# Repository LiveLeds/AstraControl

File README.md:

# AstraControl

[GitHub IO Page](https://liveleds.github.io/AstraControl)

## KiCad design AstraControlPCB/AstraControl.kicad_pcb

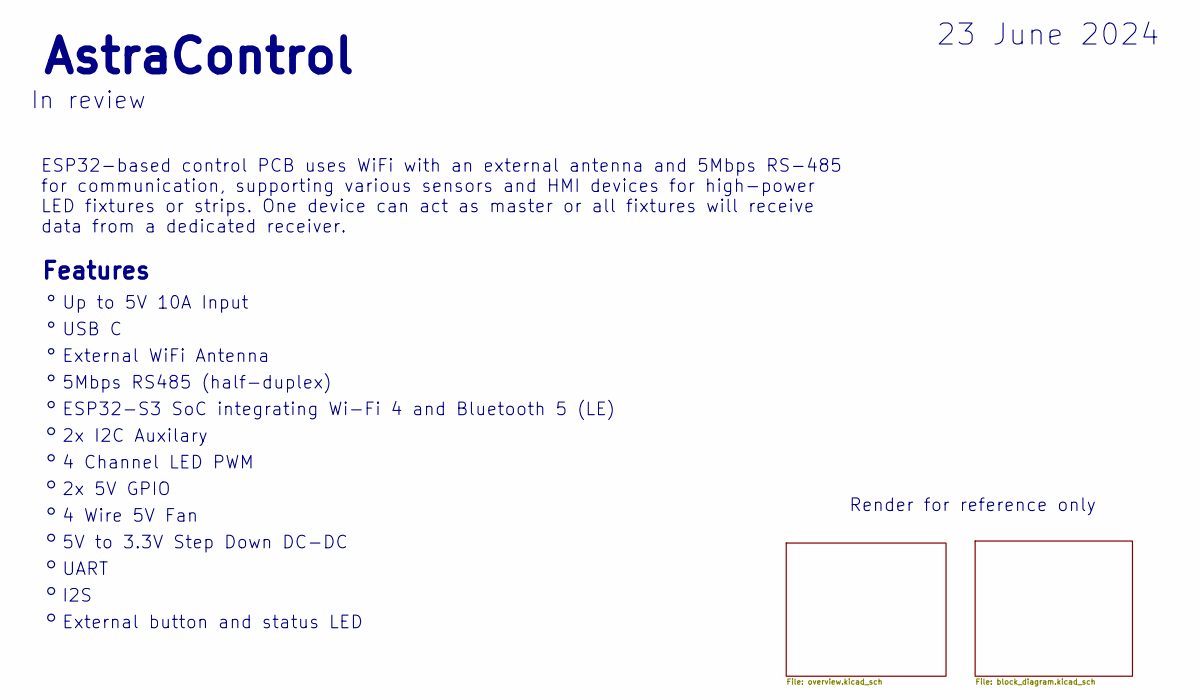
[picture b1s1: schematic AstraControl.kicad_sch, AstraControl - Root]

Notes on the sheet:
2x 5V GPIO
I2S
USB C
2x I2C Auxilary
Render for reference only
23 June 2024
ESP32-based control PCB uses WiFi with an external antenna and 5Mbps RS-485 for communication, supporting various sensors and HMI devices for high-power LED fixtures or strips. One device can act as master or all fixtures will receive data from a dedicated receiver.
AstraControl
5V to 3.3V Step Down DC-DC
External WiFi Antenna
ESP32-S3 SoC integrating Wi-Fi 4 and Bluetooth 5 (LE)
In review
Up to 5V 10A Input
4 Channel LED PWM
UART
External button and status LED
Features
5Mbps RS485 (half-duplex)
4 Wire 5V Fan

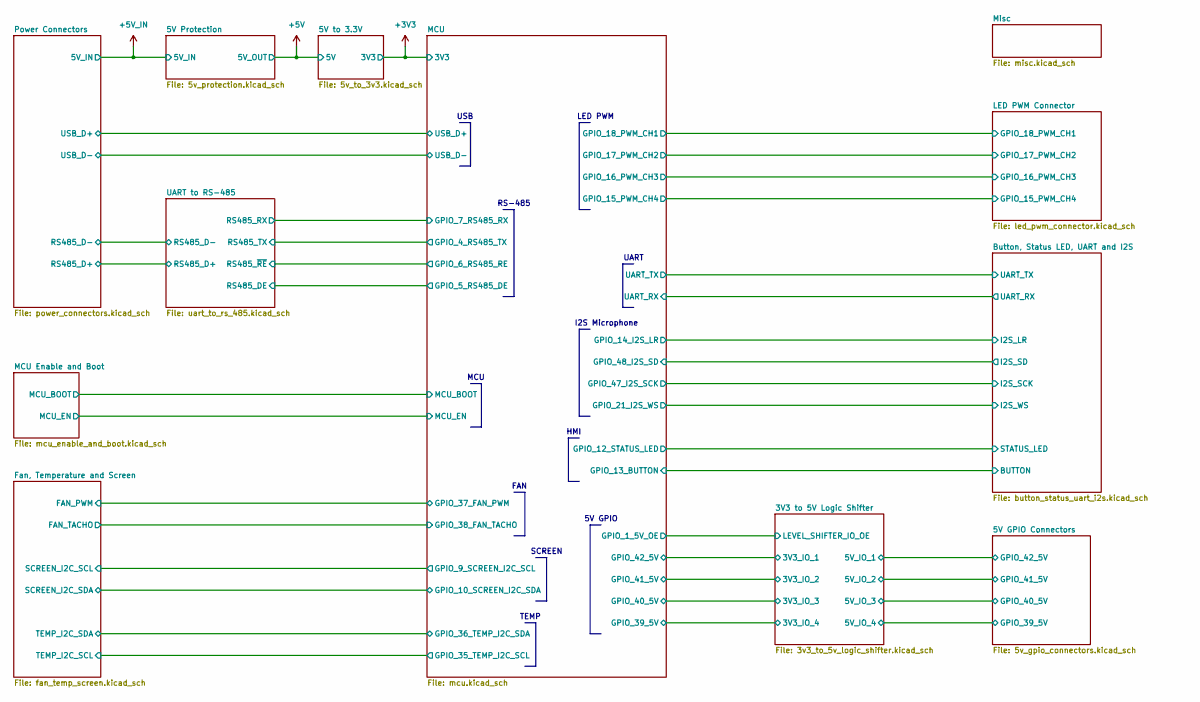
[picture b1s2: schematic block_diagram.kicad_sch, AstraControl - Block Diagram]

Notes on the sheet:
USB
FAN
LED PWM
MCU
I2S Microphone
5V GPIO
RS-485
UART
SCREEN
HMI
TEMP

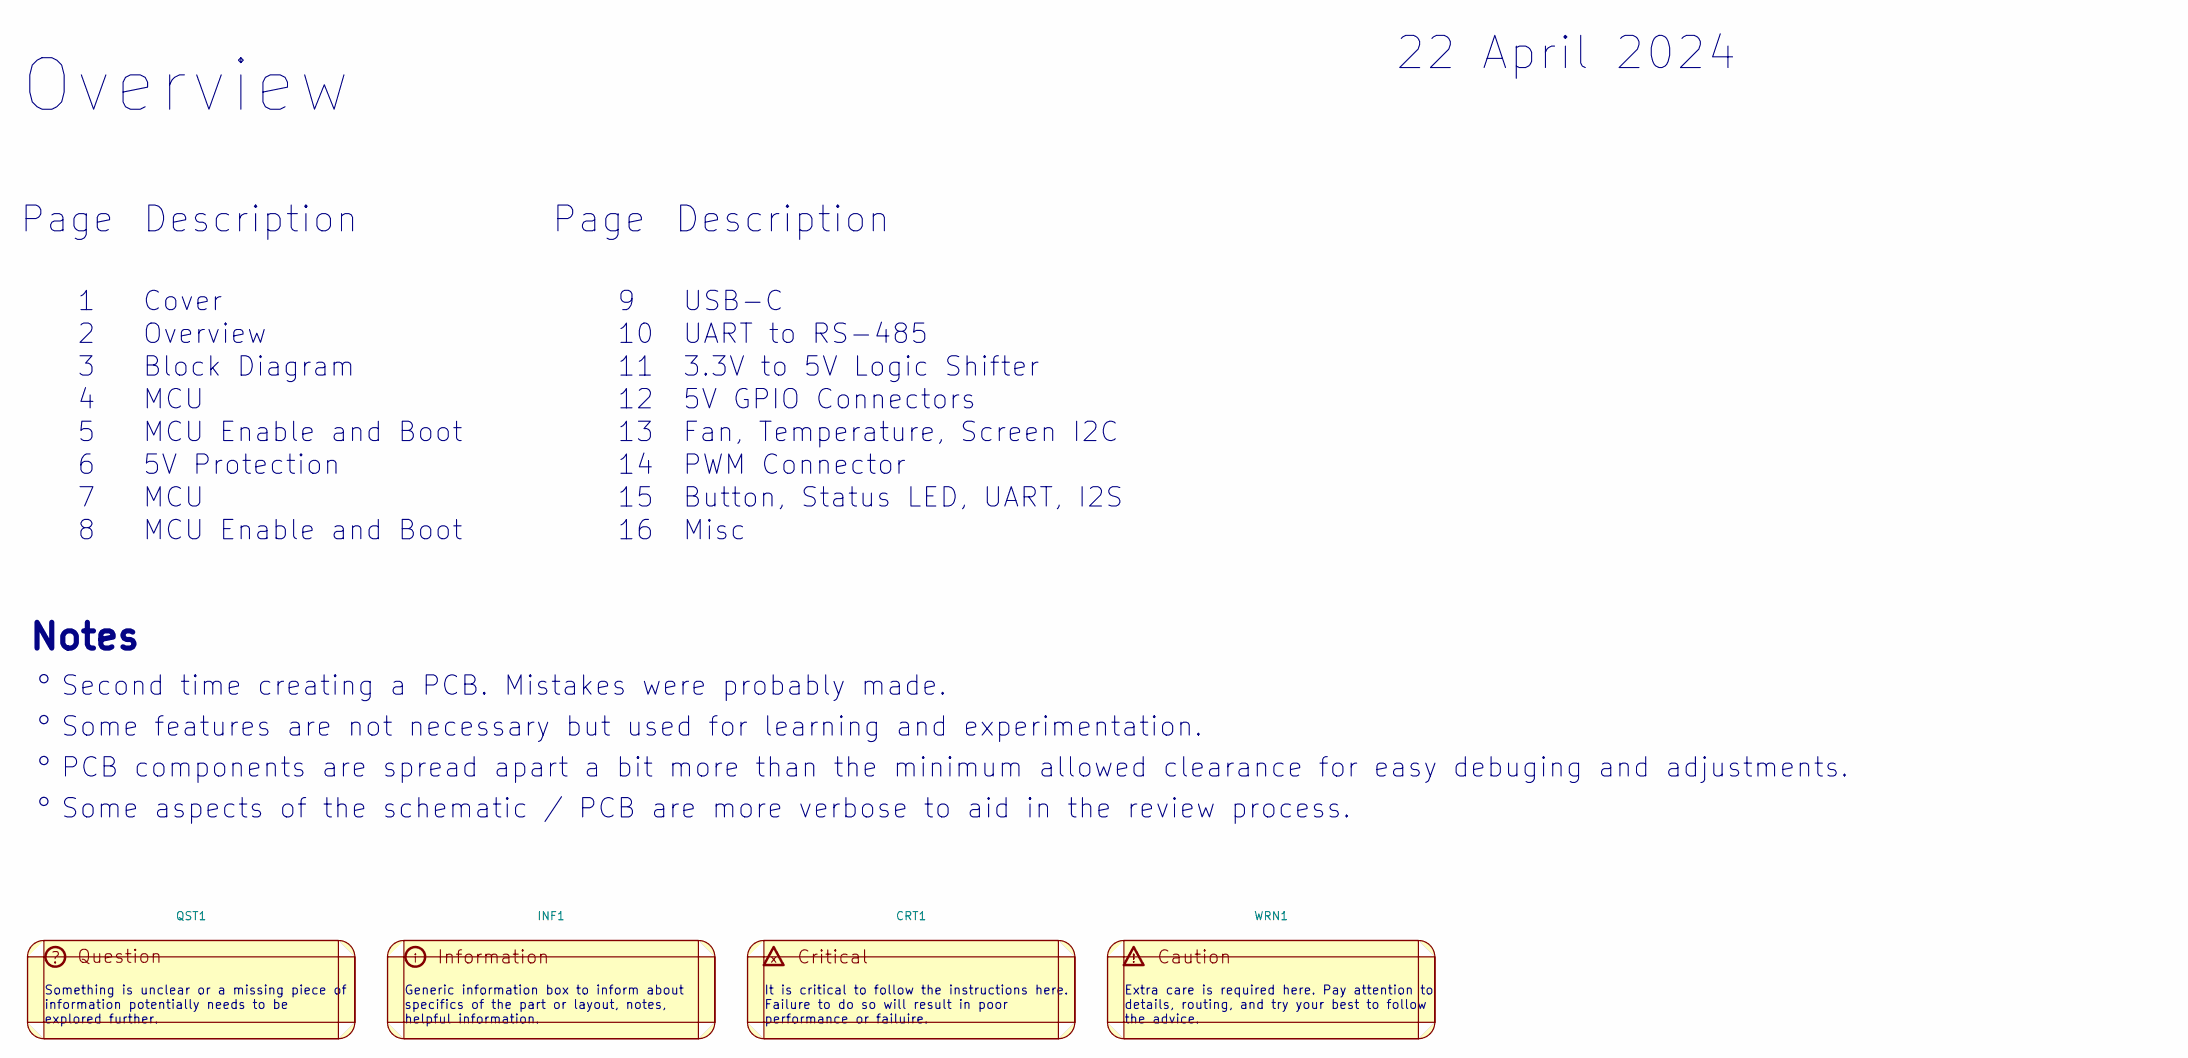
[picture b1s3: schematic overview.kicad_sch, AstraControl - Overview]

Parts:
CRT1: (no value)
INF1: (no value)
QST1: (no value)
WRN1: (no value)

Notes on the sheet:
Some features are not necessary but used for learning and experimentation.
PWM Connector
Misc
3.3V to 5V Logic Shifter
UART to RS-485
Fan, Temperature, Screen I2C
5V Protection
PCB components are spread apart a bit more than the minimum allowed clearance for easy debuging and adjustments.
Something is unclear or a missing piece of information potentially needs to be explored further.
Page
22 April 2024
MCU Enable and Boot
Notes
5V GPIO Connectors
It is critical to follow the instructions here. Failure to do so will result in poor performance or failuire.
Overview
Cover
MCU
Second time creating a PCB. Mistakes were probably made.
Description
Some aspects of the schematic / PCB are more verbose to aid in the review process.
Button, Status LED, UART, I2S
USB-C
Generic information box to inform about specifics of the part or layout, notes, helpful information.
Extra care is required here. Pay attention to details, routing, and try your best to follow the advice.
Block Diagram

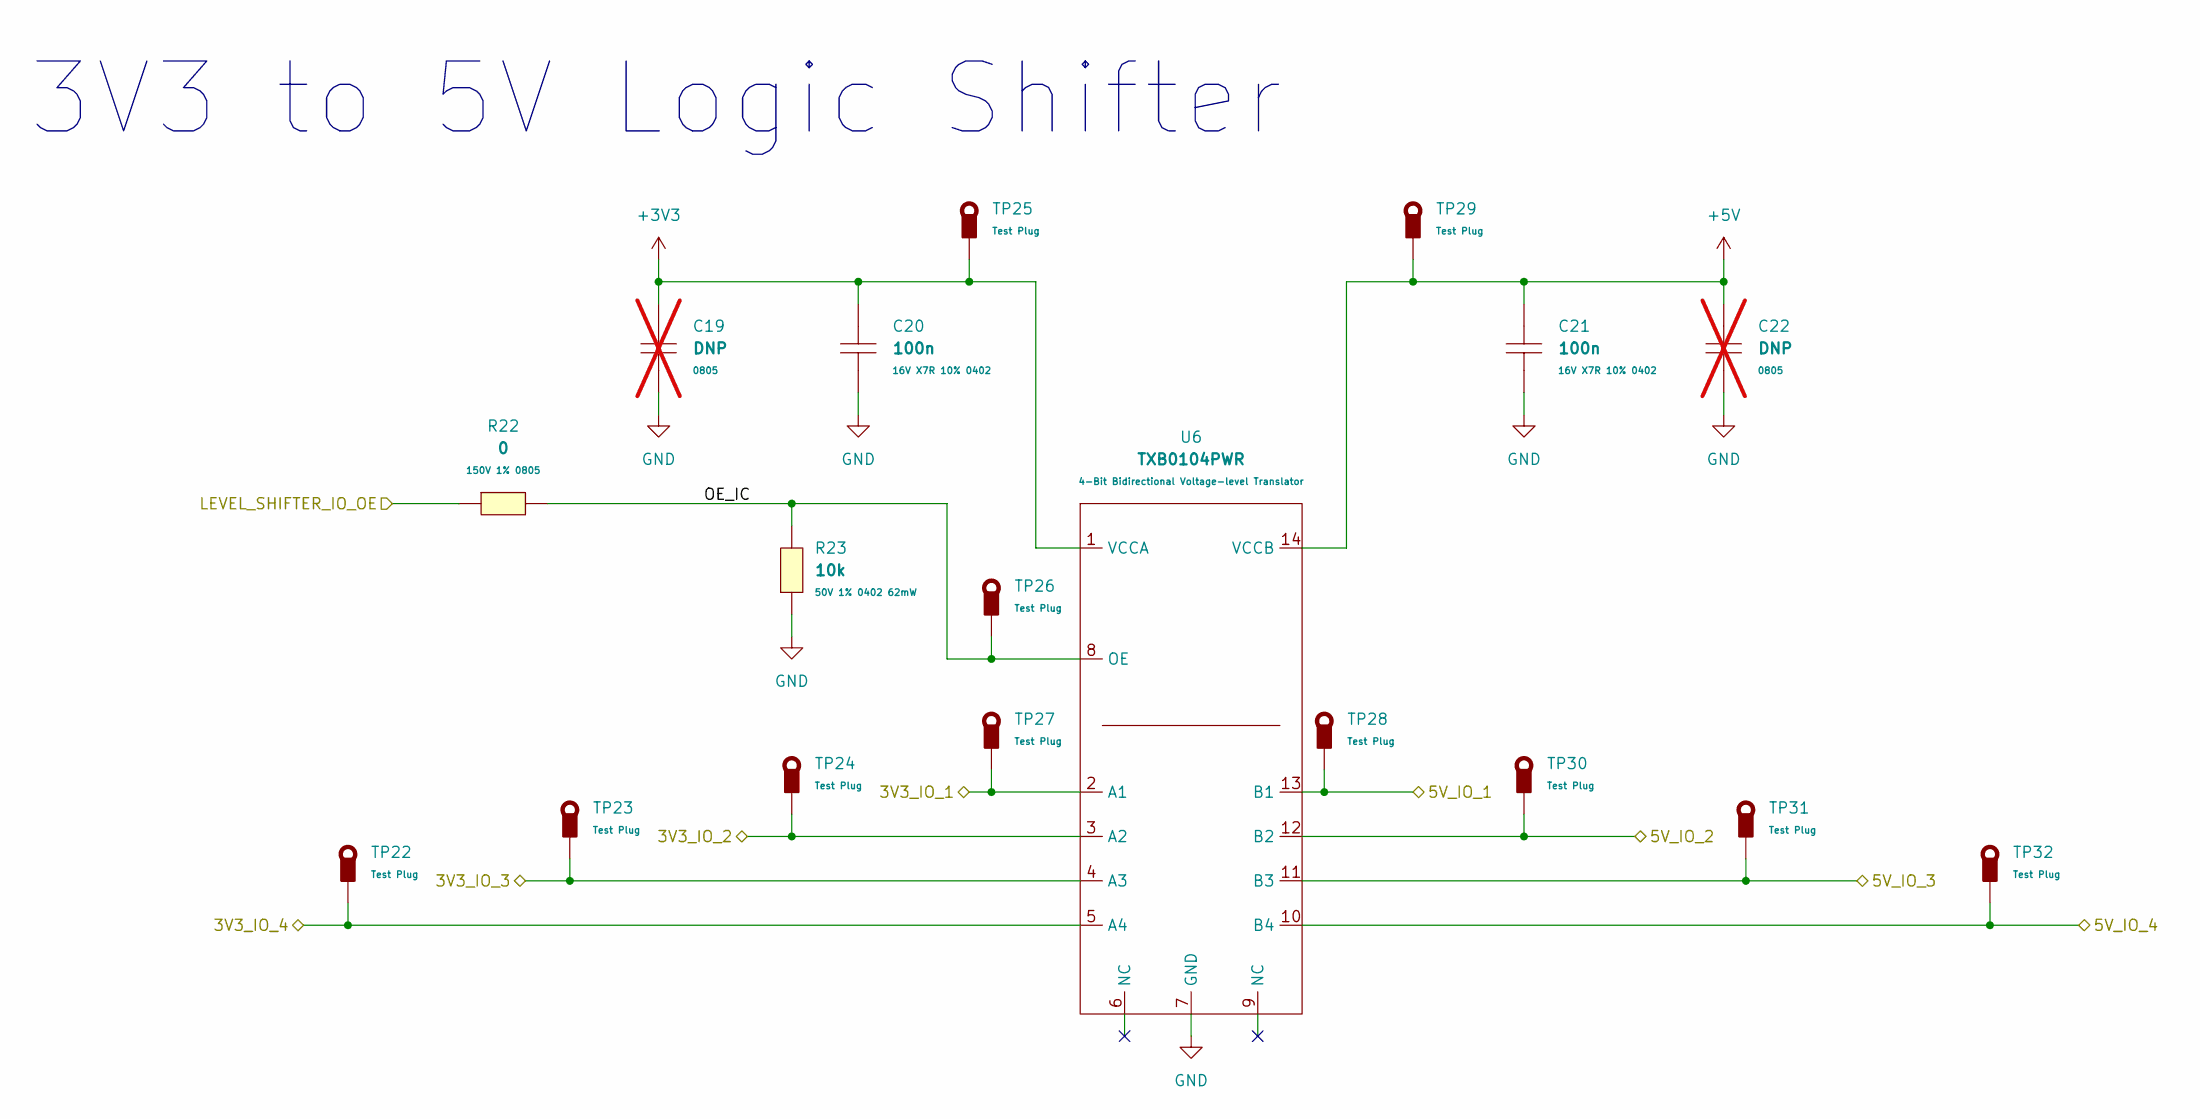
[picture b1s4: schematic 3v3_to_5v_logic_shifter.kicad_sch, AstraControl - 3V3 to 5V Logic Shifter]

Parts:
C19, C22: DNP; C_DNP_0805_2012Metric_Pad1.18x1.45mm_HandSolder; not fitted
C20, C21: 100n; C_0402_1005Metric; MPN CL05B104KO5NNNC; LCSC Part C1525
R22: 0; R_0805_2012Metric_Pad1.20x1.40mm_HandSolder; MPN 0805W8F0000T5E; LCSC Part C17477
R23: 10k; R_0402_1005Metric; MPN 0402WGF1002TCE; LCSC Part C25744
TP22, TP23, TP24, TP25, TP26, TP27, TP28, TP29, TP30, TP31, TP32: TestPoint_Thimble; TestPoint_Loop_D3.50mm_Drill0.9mm_Beaded; MPN RH-5000; LCSC Part C5277086
U6: TXB0104PWR; LOGIC_SHIFTER_TXB0104PWR_TSOP_14; MPN TXB0104PWR; LCSC Part C60708

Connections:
+3V3: C19.2, C20.2, TP25.1, U6.1 (VCCA); also elsewhere on the board
+5V: C21.2, C22.2, TP29.1, U6.14 (VCCB); also elsewhere on the board
/Block Diagram/3V3 to 5V Logic Shifter/3V3_IO_1: TP27.1, U6.2 (A1); also elsewhere on the board
/Block Diagram/3V3 to 5V Logic Shifter/3V3_IO_2: TP24.1, U6.3 (A2); also elsewhere on the board
/Block Diagram/3V3 to 5V Logic Shifter/3V3_IO_3: TP23.1, U6.4 (A3); also elsewhere on the board
/Block Diagram/3V3 to 5V Logic Shifter/3V3_IO_4: TP22.1, U6.5 (A4); also elsewhere on the board
/Block Diagram/3V3 to 5V Logic Shifter/5V_IO_1: TP28.1, U6.13 (B1); also elsewhere on the board
/Block Diagram/3V3 to 5V Logic Shifter/5V_IO_2: TP30.1, U6.12 (B2); also elsewhere on the board
/Block Diagram/3V3 to 5V Logic Shifter/5V_IO_3: TP31.1, U6.11 (B3); also elsewhere on the board
/Block Diagram/3V3 to 5V Logic Shifter/5V_IO_4: TP32.1, U6.10 (B4); also elsewhere on the board
/Block Diagram/3V3 to 5V Logic Shifter/LEVEL_SHIFTER_IO_OE: R22.1; also elsewhere on the board
/Block Diagram/3V3 to 5V Logic Shifter/OE_IC: R22.2, R23.2, TP26.1, U6.8 (OE)
GND: C19.1, C20.1, C21.1, C22.1, R23.1, U6.7 (GND); also elsewhere on the board

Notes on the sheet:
3V3 to 5V Logic Shifter

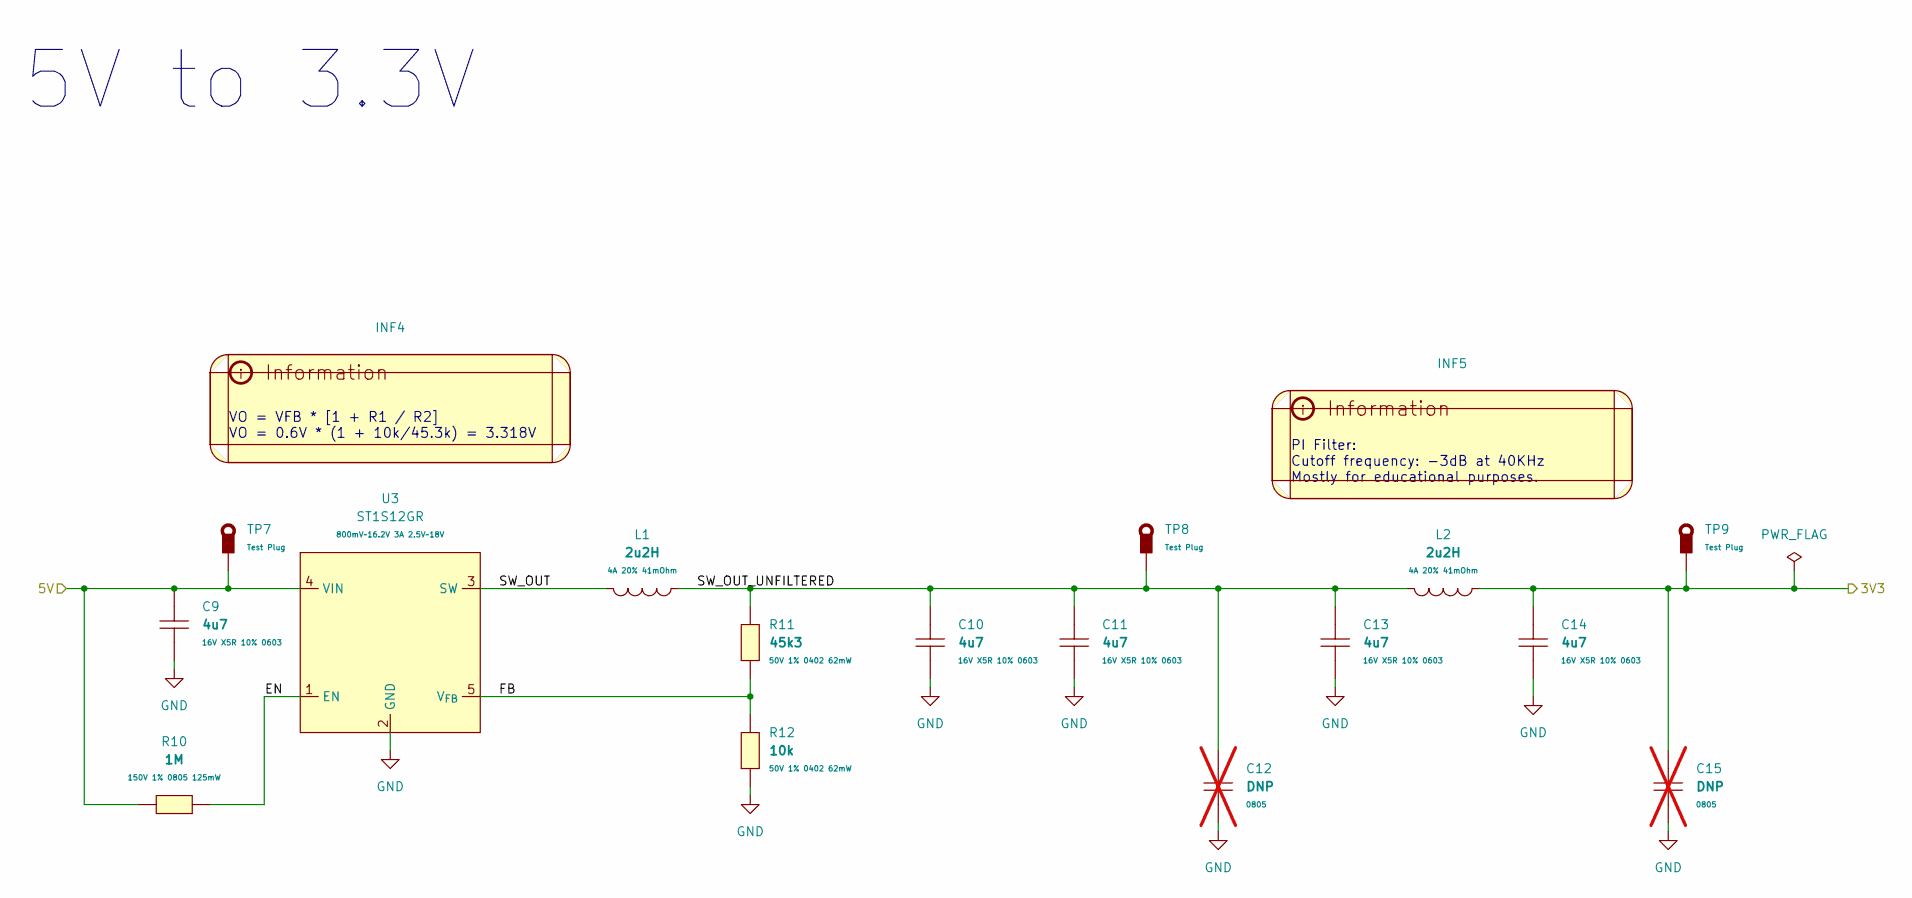
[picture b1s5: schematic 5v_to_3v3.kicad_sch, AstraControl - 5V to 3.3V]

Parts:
C9, C10, C11, C13, C14: 4u7; C_0603_1608Metric; MPN CL10A475KO8NNNC; LCSC Part C19666
C12, C15: DNP; C_DNP_0805_2012Metric_Pad1.18x1.45mm_HandSolder; not fitted
INF4, INF5: (no value)
L1, L2: 2u2H; L_MDA4020_4.1x4.5mm; MPN MDA4020-2R2M; LCSC Part C2847469
R10: 1M; R_0805_2012Metric_Pad1.20x1.40mm_HandSolder; MPN 0805W8F1004T5E; LCSC Part C17514
R11: 45k3; R_0402_1005Metric; MPN 0402WGF4532TCE; LCSC Part C26980
R12: 10k; R_0402_1005Metric; MPN 0402WGF1002TCE; LCSC Part C25744
TP7, TP8, TP9: TestPoint_Thimble; TestPoint_Loop_D3.50mm_Drill0.9mm_Beaded; MPN RH-5000; LCSC Part C5277086
U3: ST1S12GR; STEP_DOWN_ST1S12GR_TSOT-23-5; MPN ST1S12GR; LCSC Part C222072

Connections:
+3V3: C14.2, C15.2, L2.1, TP9.1; also elsewhere on the board
+5V: C9.2, R10.2, TP7.1, U3.4 (VIN); also elsewhere on the board
/Block Diagram/5V to 3.3V/EN: R10.1, U3.1 (EN)
/Block Diagram/5V to 3.3V/FB: R11.1, R12.2, U3.5 (V_{FB})
/Block Diagram/5V to 3.3V/SW_OUT: L1.2, U3.3 (SW)
/Block Diagram/5V to 3.3V/SW_OUT_UNFILTERED: C10.2, C11.2, C12.2, C13.2, L1.1, L2.2, R11.2, TP8.1
GND: C9.1, C10.1, C11.1, C12.1, C13.1, C14.1, C15.1, R12.1, U3.2 (GND); also elsewhere on the board

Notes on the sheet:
VO = VFB * [1 + R1 / R2] VO = 0.6V * (1 + 10k/45.3k) = 3.318V
5V to 3.3V
PI Filter: Cutoff frequency: -3dB at 40KHz Mostly for educational purposes.

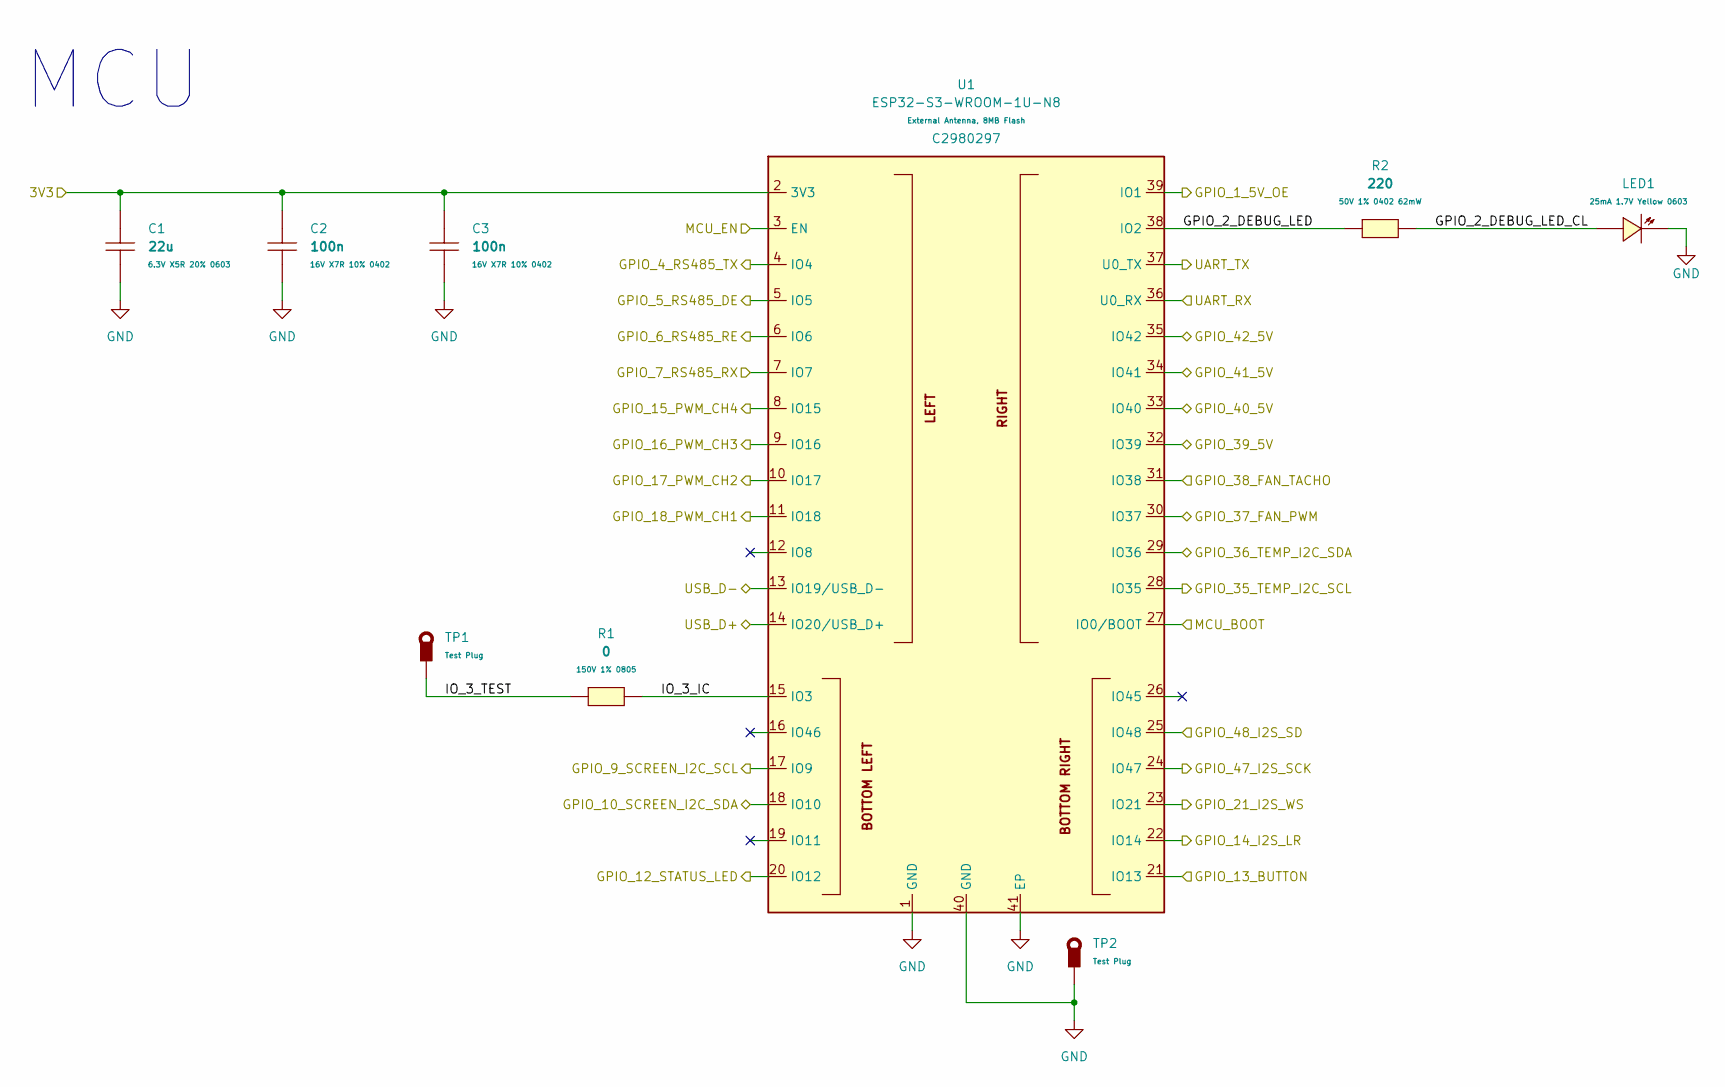
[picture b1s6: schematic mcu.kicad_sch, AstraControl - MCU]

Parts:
C1: 22u; C_0603_1608Metric; MPN CL10A226MQ8NRNC; LCSC Part C59461
C2, C3: 100n; C_0402_1005Metric; MPN CL05B104KO5NNNC; LCSC Part C1525
LED1: LED_Yellow_25mA_0603; LED_0603_1608Metric; MPN 19-213/Y2C-CQ2R2L/3T(CY); LCSC Part C72038
R1: 0; R_0805_2012Metric_Pad1.20x1.40mm_HandSolder; MPN 0805W8F0000T5E; LCSC Part C17477
R2: 220; R_0402_1005Metric; MPN 0402WGF2200TCE; LCSC Part C25091
TP1, TP2: TestPoint_Thimble; TestPoint_Loop_D3.50mm_Drill0.9mm_Beaded; MPN RH-5000; LCSC Part C5277086
U1: ESP32-S3-WROOM-1U-N8; WIRELM-SMD_ESP32-S3-WROOM-1U; MPN ESP32-S3-WROOM-1U-N8; LCSC Part C2980297

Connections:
+3V3: C1.2, C2.2, C3.2, U1.2 (3V3); also elsewhere on the board
/Block Diagram/3V3 to 5V Logic Shifter/3V3_IO_1: U1.35 (IO42); also elsewhere on the board
/Block Diagram/3V3 to 5V Logic Shifter/3V3_IO_2: U1.34 (IO41); also elsewhere on the board
/Block Diagram/3V3 to 5V Logic Shifter/3V3_IO_3: U1.33 (IO40); also elsewhere on the board
/Block Diagram/3V3 to 5V Logic Shifter/3V3_IO_4: U1.32 (IO39); also elsewhere on the board
/Block Diagram/3V3 to 5V Logic Shifter/LEVEL_SHIFTER_IO_OE: U1.39 (IO1); also elsewhere on the board
/Block Diagram/Button, Status LED, UART and I2S/BUTTON: U1.21 (IO13); also elsewhere on the board
/Block Diagram/Button, Status LED, UART and I2S/I2S_LR: U1.22 (IO14); also elsewhere on the board
/Block Diagram/Button, Status LED, UART and I2S/I2S_SCK: U1.24 (IO47); also elsewhere on the board
/Block Diagram/Button, Status LED, UART and I2S/I2S_SD: U1.25 (IO48); also elsewhere on the board
/Block Diagram/Button, Status LED, UART and I2S/I2S_WS: U1.23 (IO21); also elsewhere on the board
/Block Diagram/Button, Status LED, UART and I2S/STATUS_LED: U1.20 (IO12); also elsewhere on the board
/Block Diagram/Button, Status LED, UART and I2S/UART_RX: U1.36 (U0_RX); also elsewhere on the board
/Block Diagram/Button, Status LED, UART and I2S/UART_TX: U1.37 (U0_TX); also elsewhere on the board
/Block Diagram/Fan, Temperature and Screen/FAN_PWM: U1.30 (IO37); also elsewhere on the board
/Block Diagram/Fan, Temperature and Screen/FAN_TACHO: U1.31 (IO38); also elsewhere on the board
/Block Diagram/Fan, Temperature and Screen/SCREEN_I2C_SCL: U1.17 (IO9); also elsewhere on the board
/Block Diagram/Fan, Temperature and Screen/SCREEN_I2C_SDA: U1.18 (IO10); also elsewhere on the board
/Block Diagram/Fan, Temperature and Screen/TEMP_I2C_SCL: U1.28 (IO35); also elsewhere on the board
/Block Diagram/Fan, Temperature and Screen/TEMP_I2C_SDA: U1.29 (IO36); also elsewhere on the board
/Block Diagram/LED PWM Connector/GPIO_15_PWM_CH4: U1.8 (IO15); also elsewhere on the board
/Block Diagram/LED PWM Connector/GPIO_16_PWM_CH3: U1.9 (IO16); also elsewhere on the board
/Block Diagram/LED PWM Connector/GPIO_17_PWM_CH2: U1.10 (IO17); also elsewhere on the board
/Block Diagram/LED PWM Connector/GPIO_18_PWM_CH1: U1.11 (IO18); also elsewhere on the board
/Block Diagram/MCU Enable and Boot/MCU_BOOT: U1.27 (IO0/BOOT); also elsewhere on the board
/Block Diagram/MCU Enable and Boot/MCU_EN: U1.3 (EN); also elsewhere on the board
/Block Diagram/MCU/GPIO_2_DEBUG_LED: R2.1, U1.38 (IO2)
/Block Diagram/MCU/GPIO_2_DEBUG_LED_CL: LED1.2 (A), R2.2
/Block Diagram/MCU/GPIO_4_RS485_TX: U1.4 (IO4); also elsewhere on the board
/Block Diagram/MCU/GPIO_5_RS485_DE: U1.5 (IO5); also elsewhere on the board
/Block Diagram/MCU/GPIO_6_RS485_RE: U1.6 (IO6); also elsewhere on the board
/Block Diagram/MCU/GPIO_7_RS485_RX: U1.7 (IO7); also elsewhere on the board
/Block Diagram/MCU/IO_3_IC: R1.2, U1.15 (IO3)
/Block Diagram/MCU/IO_3_TEST: R1.1, TP1.1
/Block Diagram/MCU/USB_D+: U1.14 (IO20/USB_D+); also elsewhere on the board
/Block Diagram/MCU/USB_D-: U1.13 (IO19/USB_D-); also elsewhere on the board
GND: C1.1, C2.1, C3.1, LED1.1 (K), TP2.1, U1.1 (GND), U1.40 (GND), U1.41 (EP); also elsewhere on the board

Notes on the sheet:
MCU

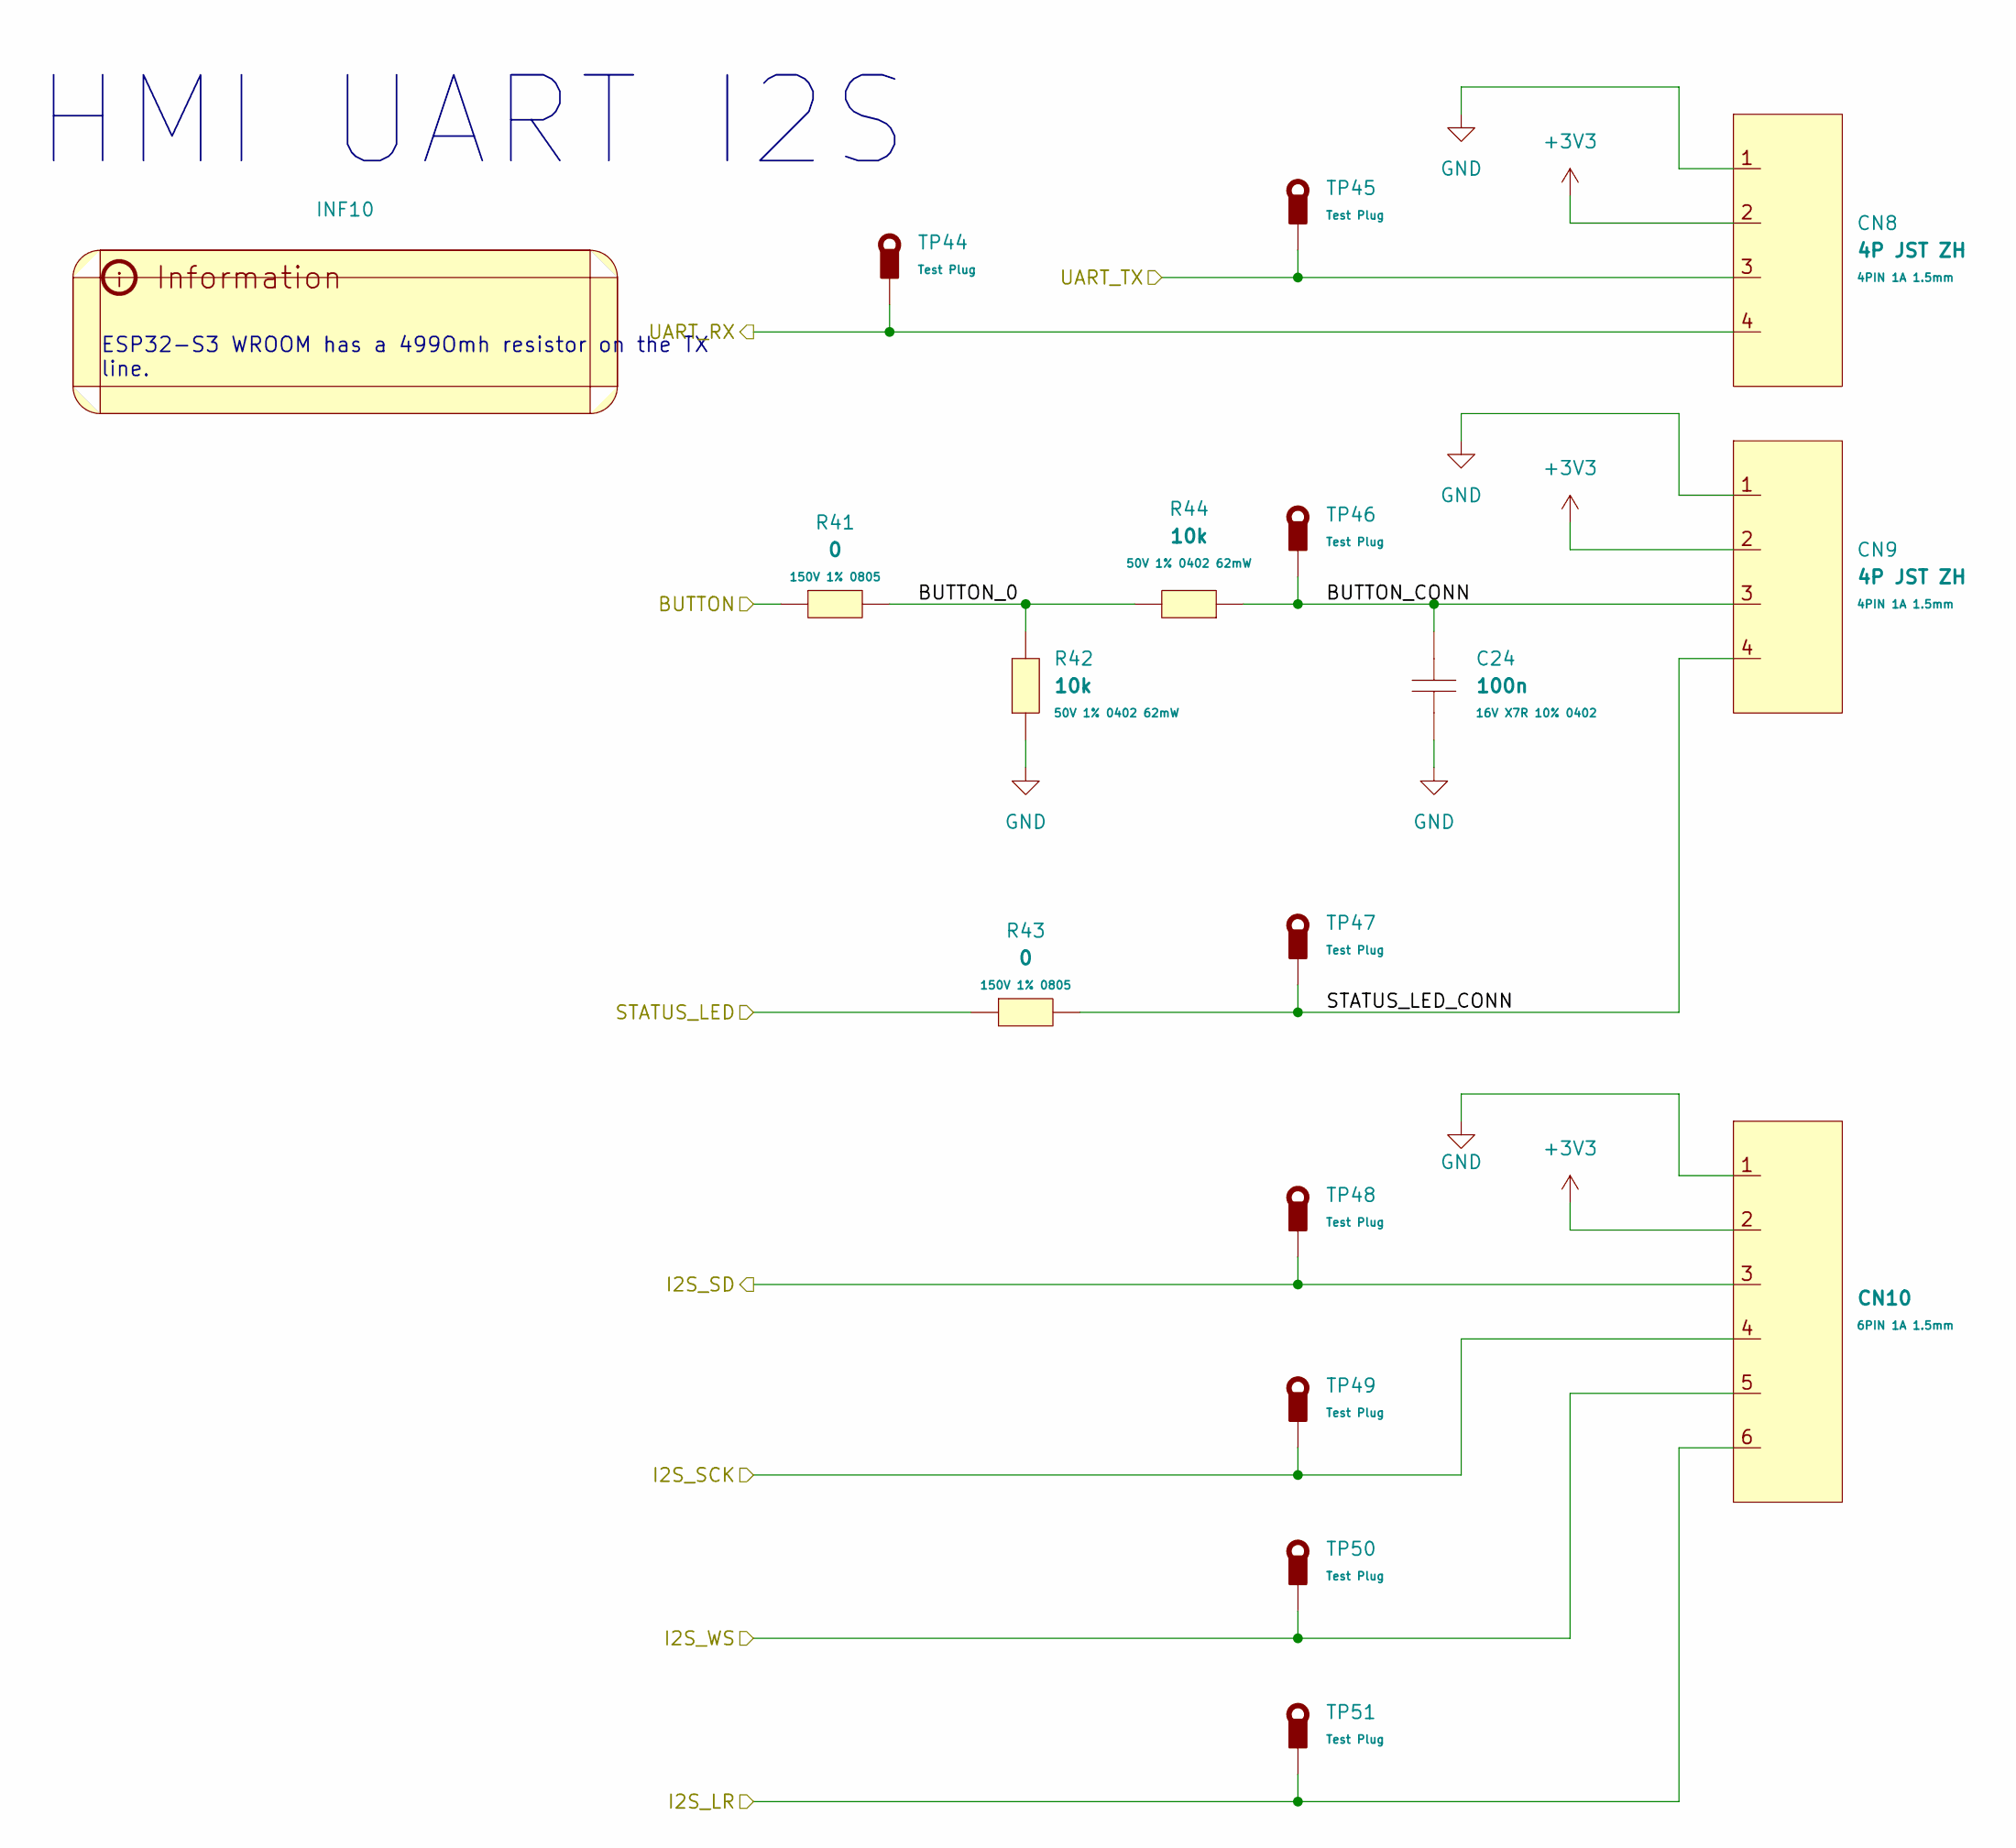
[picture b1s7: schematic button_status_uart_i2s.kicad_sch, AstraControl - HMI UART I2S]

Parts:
C24: 100n; C_0402_1005Metric; MPN CL05B104KO5NNNC; LCSC Part C1525
CN8, CN9: 4P JST ZH; JST_ZH_B4B-ZR_1x04_P1.50mm_Vertical; MPN B4B-ZR-3.4(LF)(SN); LCSC Part C163034
CN10: JST_ZH_6PIN_1A_250V; JST_ZH_B6B-ZR_1x06_P1.50mm_Vertical; MPN B6B-ZR(LF)(SN); LCSC Part C157984
INF10: (no value)
R41, R43: 0; R_0805_2012Metric_Pad1.20x1.40mm_HandSolder; MPN 0805W8F0000T5E; LCSC Part C17477
R42, R44: 10k; R_0402_1005Metric; MPN 0402WGF1002TCE; LCSC Part C25744
TP44, TP45, TP46, TP47, TP48, TP49, TP50, TP51: TestPoint_Thimble; TestPoint_Loop_D3.50mm_Drill0.9mm_Beaded; MPN RH-5000; LCSC Part C5277086

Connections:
+3V3: CN8.2, CN9.2, CN10.2; also elsewhere on the board
/Block Diagram/Button, Status LED, UART and I2S/BUTTON: R41.1; also elsewhere on the board
/Block Diagram/Button, Status LED, UART and I2S/BUTTON_0: R41.2, R42.2, R44.2
/Block Diagram/Button, Status LED, UART and I2S/BUTTON_CONN: C24.2, CN9.3, R44.1, TP46.1
/Block Diagram/Button, Status LED, UART and I2S/I2S_LR: CN10.6, TP51.1; also elsewhere on the board
/Block Diagram/Button, Status LED, UART and I2S/I2S_SCK: CN10.4, TP49.1; also elsewhere on the board
/Block Diagram/Button, Status LED, UART and I2S/I2S_SD: CN10.3, TP48.1; also elsewhere on the board
/Block Diagram/Button, Status LED, UART and I2S/I2S_WS: CN10.5, TP50.1; also elsewhere on the board
/Block Diagram/Button, Status LED, UART and I2S/STATUS_LED: R43.1; also elsewhere on the board
/Block Diagram/Button, Status LED, UART and I2S/STATUS_LED_CONN: CN9.4, R43.2, TP47.1
/Block Diagram/Button, Status LED, UART and I2S/UART_RX: CN8.4, TP44.1; also elsewhere on the board
/Block Diagram/Button, Status LED, UART and I2S/UART_TX: CN8.3, TP45.1; also elsewhere on the board
GND: C24.1, CN8.1, CN9.1, CN10.1, R42.1; also elsewhere on the board

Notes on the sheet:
ESP32-S3 WROOM has a 499Omh resistor on the TX line.
HMI UART I2S
